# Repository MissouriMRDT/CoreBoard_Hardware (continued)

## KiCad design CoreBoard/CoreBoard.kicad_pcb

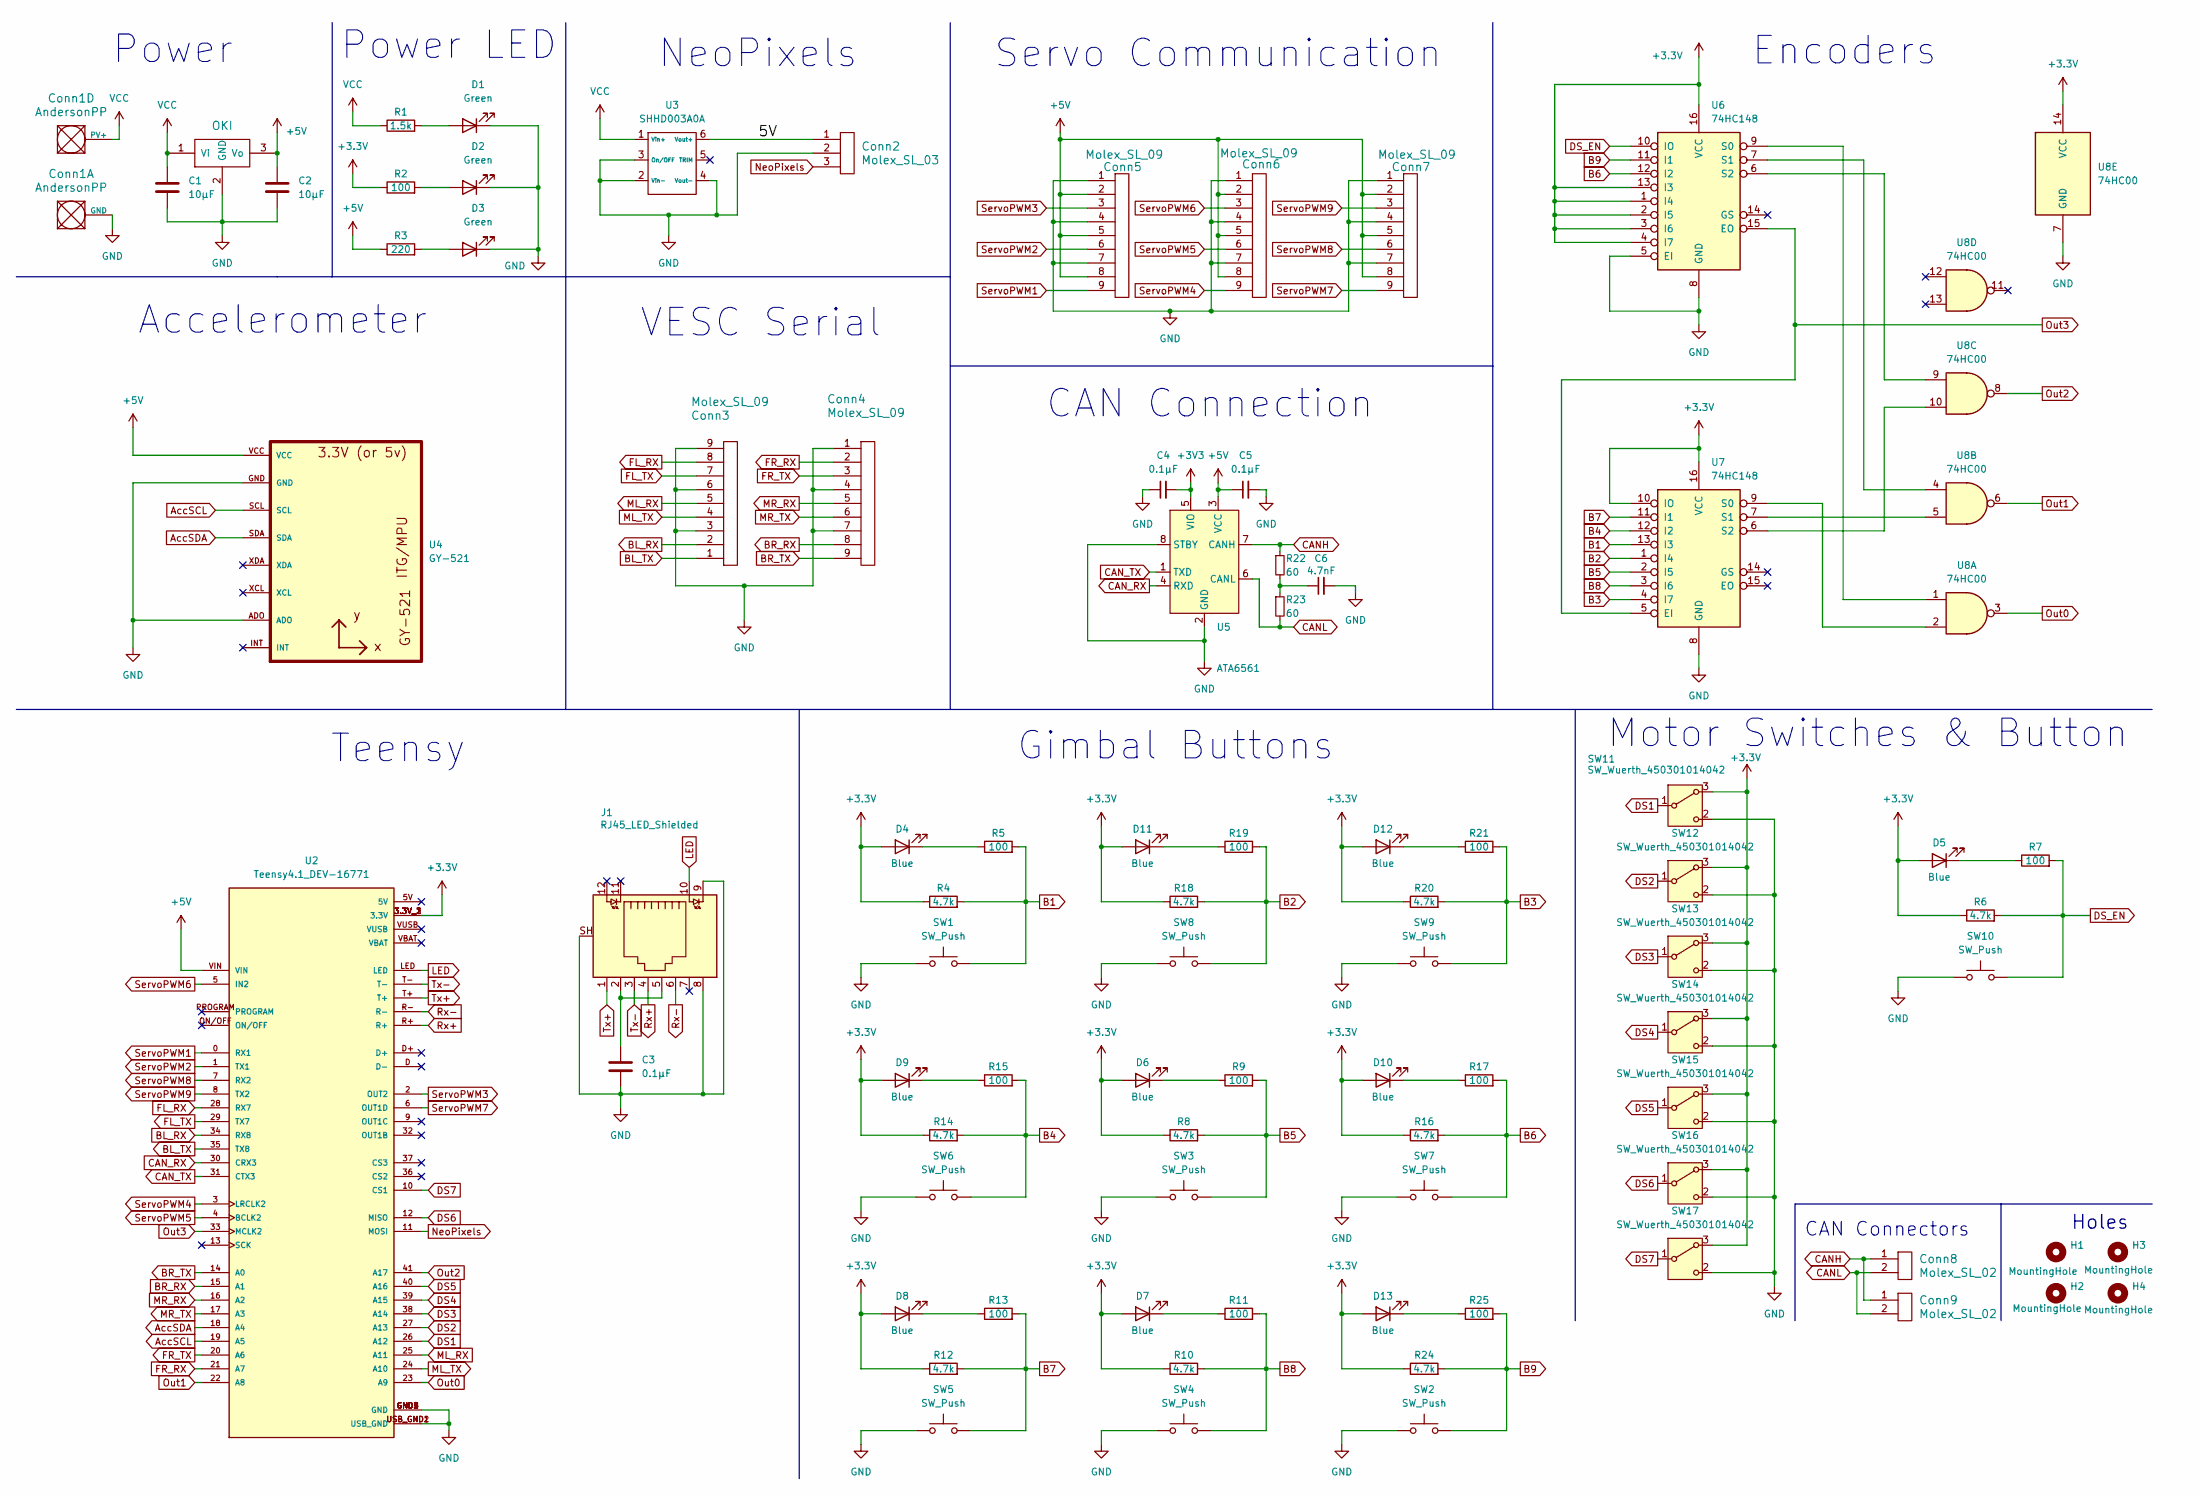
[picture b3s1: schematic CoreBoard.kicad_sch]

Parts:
C1: 10µF; C_1206_3216Metric_Pad1.33x1.80mm_HandSolder
C2: 10µF; C_0603_1608Metric_Pad1.08x0.95mm_HandSolder
C3, C4, C5: 0.1µF; C_0603_1608Metric_Pad1.08x0.95mm_HandSolder
C6: 4.7nF; C_0603_1608Metric_Pad1.08x0.95mm_HandSolder
Conn1: AndersonPP; Square_Anderson_2_H_Side_By_Side_PV
Conn2: Molex_SL_03; MOLEX_SL_03_Vertical
Conn3, Conn4, Conn5, Conn6, Conn7: Molex_SL_09; MOLEX_SL_09_Horizontal
Conn8, Conn9: Molex_SL_02; MOLEX_SL_02_Vertical
D1, D2, D3: Green; LED_0603_1608Metric_Pad1.05x0.95mm_HandSolder
D4, D5, D6, D7, D8, D9, D10, D11, D12, D13: Blue; LED_0603_1608Metric_Pad1.05x0.95mm_HandSolder
H1, H2, H3, H4: MountingHole; 4_40_Hole
J1: RJ45_LED_Shielded; RJ45_Teensy
R1: 1.5k; R_0603_1608Metric_Pad0.98x0.95mm_HandSolder
R2, R5, R7, R9, R11, R13, R15, R17, R19, R21, R25: 100; R_0603_1608Metric_Pad0.98x0.95mm_HandSolder
R3: 220; R_0603_1608Metric_Pad0.98x0.95mm_HandSolder
R4, R6, R8, R10, R12, R14, R16, R18, R20, R24: 4.7k; R_0603_1608Metric_Pad0.98x0.95mm_HandSolder
R22, R23: 60; R_0603_1608Metric_Pad0.98x0.95mm_HandSolder
SW1, SW2, SW3, SW4, SW5, SW6, SW7, SW8, SW9, SW10: SW_Push; SW_SPST_TL3305A
SW11, SW12, SW13, SW14, SW15, SW16, SW17: SW_Wuerth_450301014042; SW_Switch_03_STSSS9121_Through_Hole
U1: OKI; OKI_Horizontal
U2: Teensy4.1_DEV-16771; Teensy_4_1_Ethernet; PARTREV 4.1
U3: SHHD003A0A; SHHD003A0A41Z_Through_Hole
U4: GY-521
U5: ATA6561; SOIC-8_3.9x4.9mm_P1.27mm
U6, U7: 74HC148; SOIC-16_4.55x10.3mm_P1.27mm
U8: 74HC00; SO-14_5.3x10.2mm_P1.27mm

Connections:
+3.3V: D4.2 (A), D5.2 (A), D6.2 (A), D7.2 (A), D8.2 (A), D9.2 (A), D10.2 (A), D11.2 (A), D12.2 (A), D13.2 (A), R2.1, R4.1, R6.1, R8.1, R10.1, R12.1, R14.1, R16.1, R18.1, R20.1, R24.1, SW11.3 (A), SW12.3 (A), SW13.3 (A), SW14.3 (A), SW15.3 (A), SW16.3 (A), SW17.3 (A), U2.3.3V_1 (3.3V), U2.3.3V_2 (3.3V), U2.3.3V_3 (3.3V), U6.1 (I4), U6.2 (I5), U6.3 (I6), U6.4 (I7), U6.13 (I3), U6.16 (VCC), U7.10 (IO), U7.16 (VCC), U8.14 (VCC)
+3V3: C4.2, U5.5 (VIO)
+5V: C2.1, C5.1, Conn5.2, Conn5.5, Conn5.8, Conn6.2, Conn6.5, Conn6.8, Conn7.2, Conn7.5, Conn7.8, R3.1, U1.3 (Vo), U2.VIN, U4.VCC, U5.3 (VCC)
/5V: Conn2.1, U3.6 (Vout+)
AccSCL: U2.19 (A5), U4.SCL
AccSDA: U2.18 (A4), U4.SDA
B1: R4.2, R5.2, SW1.2, U7.13 (I3)
B2: R18.2, R19.2, SW8.2, U7.1 (I4)
B3: R20.2, R21.2, SW9.2, U7.4 (I7)
B4: R14.2, R15.2, SW6.2, U7.12 (I2)
B5: R8.2, R9.2, SW3.2, U7.2 (I5)
B6: R16.2, R17.2, SW7.2, U6.12 (I2)
B7: R12.2, R13.2, SW5.2, U7.11 (I1)
B8: R10.2, R11.2, SW4.2, U7.3 (I6)
B9: R24.2, R25.2, SW2.2, U6.11 (I1)
BL_RX: Conn3.2, U2.34 (RX8)
BL_TX: Conn3.1, U2.35 (TX8)
BR_RX: Conn4.8, U2.15 (A1)
BR_TX: Conn4.9, U2.14 (A0)
CANH: Conn8.1, Conn9.1, R22.1, U5.7 (CANH)
CANL: Conn8.2, Conn9.2, R23.2, U5.6 (CANL)
CAN_RX: U2.30 (CRX3), U5.4 (RXD)
CAN_TX: U2.31 (CTX3), U5.1 (TXD)
DS1: SW11.1 (B), U2.26 (A12)
DS2: SW12.1 (B), U2.27 (A13)
DS3: SW13.1 (B), U2.38 (A14)
DS4: SW14.1 (B), U2.39 (A15)
DS5: SW15.1 (B), U2.40 (A16)
DS6: SW16.1 (B), U2.12 (MISO)
DS7: SW17.1 (B), U2.10 (CS1)
DS_EN: R6.2, R7.2, SW10.2, U6.10 (IO)
FL_RX: Conn3.8, U2.28 (RX7)
FL_TX: Conn3.7, U2.29 (TX7)
FR_RX: Conn4.2, U2.21 (A7)
FR_TX: Conn4.3, U2.20 (A6)
GND: C1.2, C2.2, C3.2, C4.1, C5.2, C6.2, Conn1.1 (GND), Conn2.2, Conn3.3, Conn3.6, Conn3.9, Conn4.1, Conn4.4, Conn4.7, Conn5.1, Conn5.4, Conn5.7, Conn6.1, Conn6.4, Conn6.7, Conn7.1, Conn7.4, Conn7.7, D1.1 (K), D2.1 (K), D3.1 (K), J1.8, J1.9, J1.SH, SW1.1, SW2.1, SW3.1, SW4.1, SW5.1, SW6.1, SW7.1, SW8.1, SW9.1, SW10.1, SW11.2 (C), SW12.2 (C), SW13.2 (C), SW14.2 (C), SW15.2 (C), SW16.2 (C), SW17.2 (C), U1.2 (GND), U2.GND1 (GND), U2.GND2 (GND), U2.GND3 (GND), U2.GND4 (GND), U2.GND5 (GND), U2.USB_GND1 (USB_GND), U2.USB_GND2 (USB_GND), U3.2 (Vin-), U3.3 (On/OFF), U3.4 (Vout-), U4.ADO, U4.GND, U5.2 (GND), U5.8 (STBY), U6.5 (EI), U6.8 (GND), U7.8 (GND), U8.7 (GND)
LED: J1.10, U2.LED
ML_RX: Conn3.5, U2.25 (A11)
ML_TX: Conn3.4, U2.24 (A10)
MR_RX: Conn4.5, U2.16 (A2)
MR_TX: Conn4.6, U2.17 (A3)
NeoPixels: Conn2.3, U2.11 (MOSI)
unnamed: C3.1, J1.2, J1.5
unnamed: C6.1, R22.2, R23.1
unnamed: D1.2 (A), R1.2
unnamed: D2.2 (A), R2.2
unnamed: D3.2 (A), R3.2
unnamed: D4.1 (K), R5.1
unnamed: D5.1 (K), R7.1
unnamed: D6.1 (K), R9.1
unnamed: D7.1 (K), R11.1
unnamed: D8.1 (K), R13.1
unnamed: D9.1 (K), R15.1
unnamed: D10.1 (K), R17.1
unnamed: D11.1 (K), R19.1
unnamed: D12.1 (K), R21.1
unnamed: D13.1 (K), R25.1
unnamed: U6.9 (S0), U8.1
unnamed: U6.7 (S1), U8.4
unnamed: U6.6 (S2), U8.9
unnamed: U7.9 (S0), U8.2
unnamed: U7.7 (S1), U8.5
unnamed: U7.6 (S2), U8.10
Out0: U2.23 (A9), U8.3
Out1: U2.22 (A8), U8.6
Out2: U2.41 (A17), U8.8
Out3: U2.33 (MCLK2), U6.15 (EO), U7.5 (EI)
Rx+: J1.4, U2.R+
Rx-: J1.6, U2.R-
ServoPWM1: Conn5.9, U2.0 (RX1)
ServoPWM2: Conn5.6, U2.1 (TX1)
ServoPWM3: Conn5.3, U2.2 (OUT2)
ServoPWM4: Conn6.9, U2.3 (LRCLK2)
ServoPWM5: Conn6.6, U2.4 (BCLK2)
ServoPWM6: Conn6.3, U2.5 (IN2)
ServoPWM7: Conn7.9, U2.6 (OUT1D)
ServoPWM8: Conn7.6, U2.7 (RX2)
ServoPWM9: Conn7.3, U2.8 (TX2)
Tx+: J1.1, U2.T+
Tx-: J1.3, U2.T-
VCC: C1.1, Conn1.4 (PV+), R1.1, U1.1 (Vi), U3.1 (Vin+)

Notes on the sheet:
Power
CAN Connection
Power LED
Gimbal Buttons
Accelerometer
Motor Switches & Button
Servo Communication
VESC Serial
Teensy
Encoders
CAN Connectors
NeoPixels
Holes

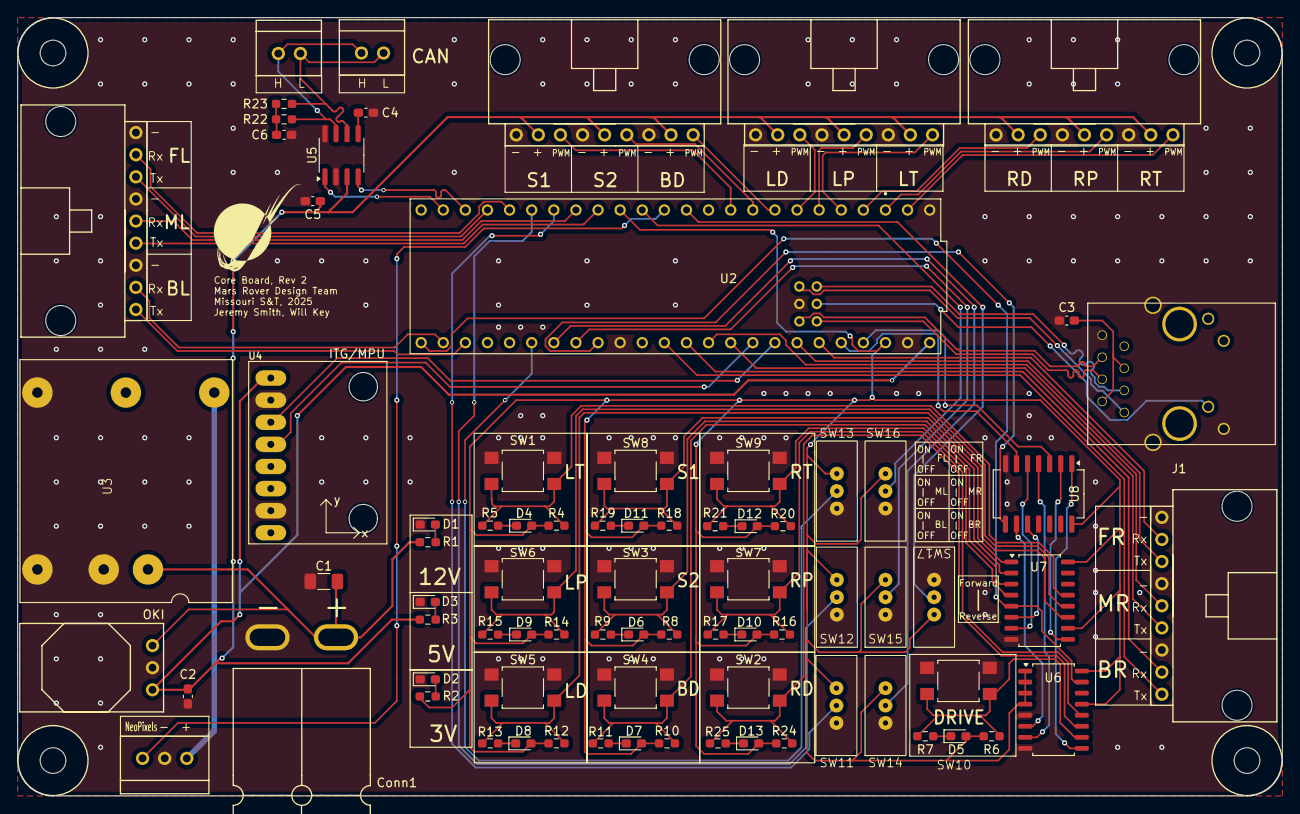
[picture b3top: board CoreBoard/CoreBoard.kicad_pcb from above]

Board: 2 copper layers, 145.3 x 89.4 mm, 83 parts (0 on the bottom side), 81 nets.

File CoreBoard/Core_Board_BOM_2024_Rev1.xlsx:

Designator | Package | Value | Item Name | Manufacturer number | Part Number | Vendor | Quantity | Cost Per Item | Cost | URL
C1,C2 |  | 10µF |  |  |  |  | 2
C3 |  | 0.1µF |  |  |  |  | 1
C4,C5 |  | 100nF |  |  |  |  | 2
C6 |  | 4.7nF |  |  |  |  | 1
Conn1 |  | AndersonPP |  |  |  |  | 1
Conn2 |  | Molex_SL_03 |  |  |  |  | 1
Conn3,Conn4,Conn5,Conn6,Conn7 |  | Molex_SL_09 |  |  |  |  | 5
D1,D2,D3 |  | Green |  |  |  |  | 3
D4,D5,D6,D7,D8,D9,D10,D11,D12,D13 |  | Blue |  |  |  |  | 10
J1 |  | RJ45_LED_Shielded |  |  |  |  | 1
R1 |  | 1.5k? |  |  |  |  | 1
R2,R5,R7,R9,R11,R13,R15,R17,R19,R21,R25 |  | 100? |  |  |  |  | 11
R3 |  | 200? |  |  |  |  | 1
R4,R6,R8,R10,R12,R14,R16,R18,R20,R24 |  | 4.7k? |  |  |  |  | 10
R22,R23 |  | 60? |  |  |  |  | 2
SW1,SW2,SW3,SW4,SW5,SW6,SW7,SW8,SW9,SW10 |  | SW_Push |  |  |  |  | 10
SW12 |  | SW_DIP_x07 |  |  |  |  | 1
U1 |  | OKI |  |  |  |  | 1
U2 |  | Teensy4.1_DEV-16771 |  |  |  |  | 1
U3 |  | SHHD003A0A |  |  |  |  | 1
U4 |  | GY-521 |  |  |  |  | 1
U5 |  | ATA6561 |  |  |  |  | 1
U6,U7 |  | 74HC148 |  |  |  |  | 2
U8 |  | 74HC00 |  |  |  |  | 1

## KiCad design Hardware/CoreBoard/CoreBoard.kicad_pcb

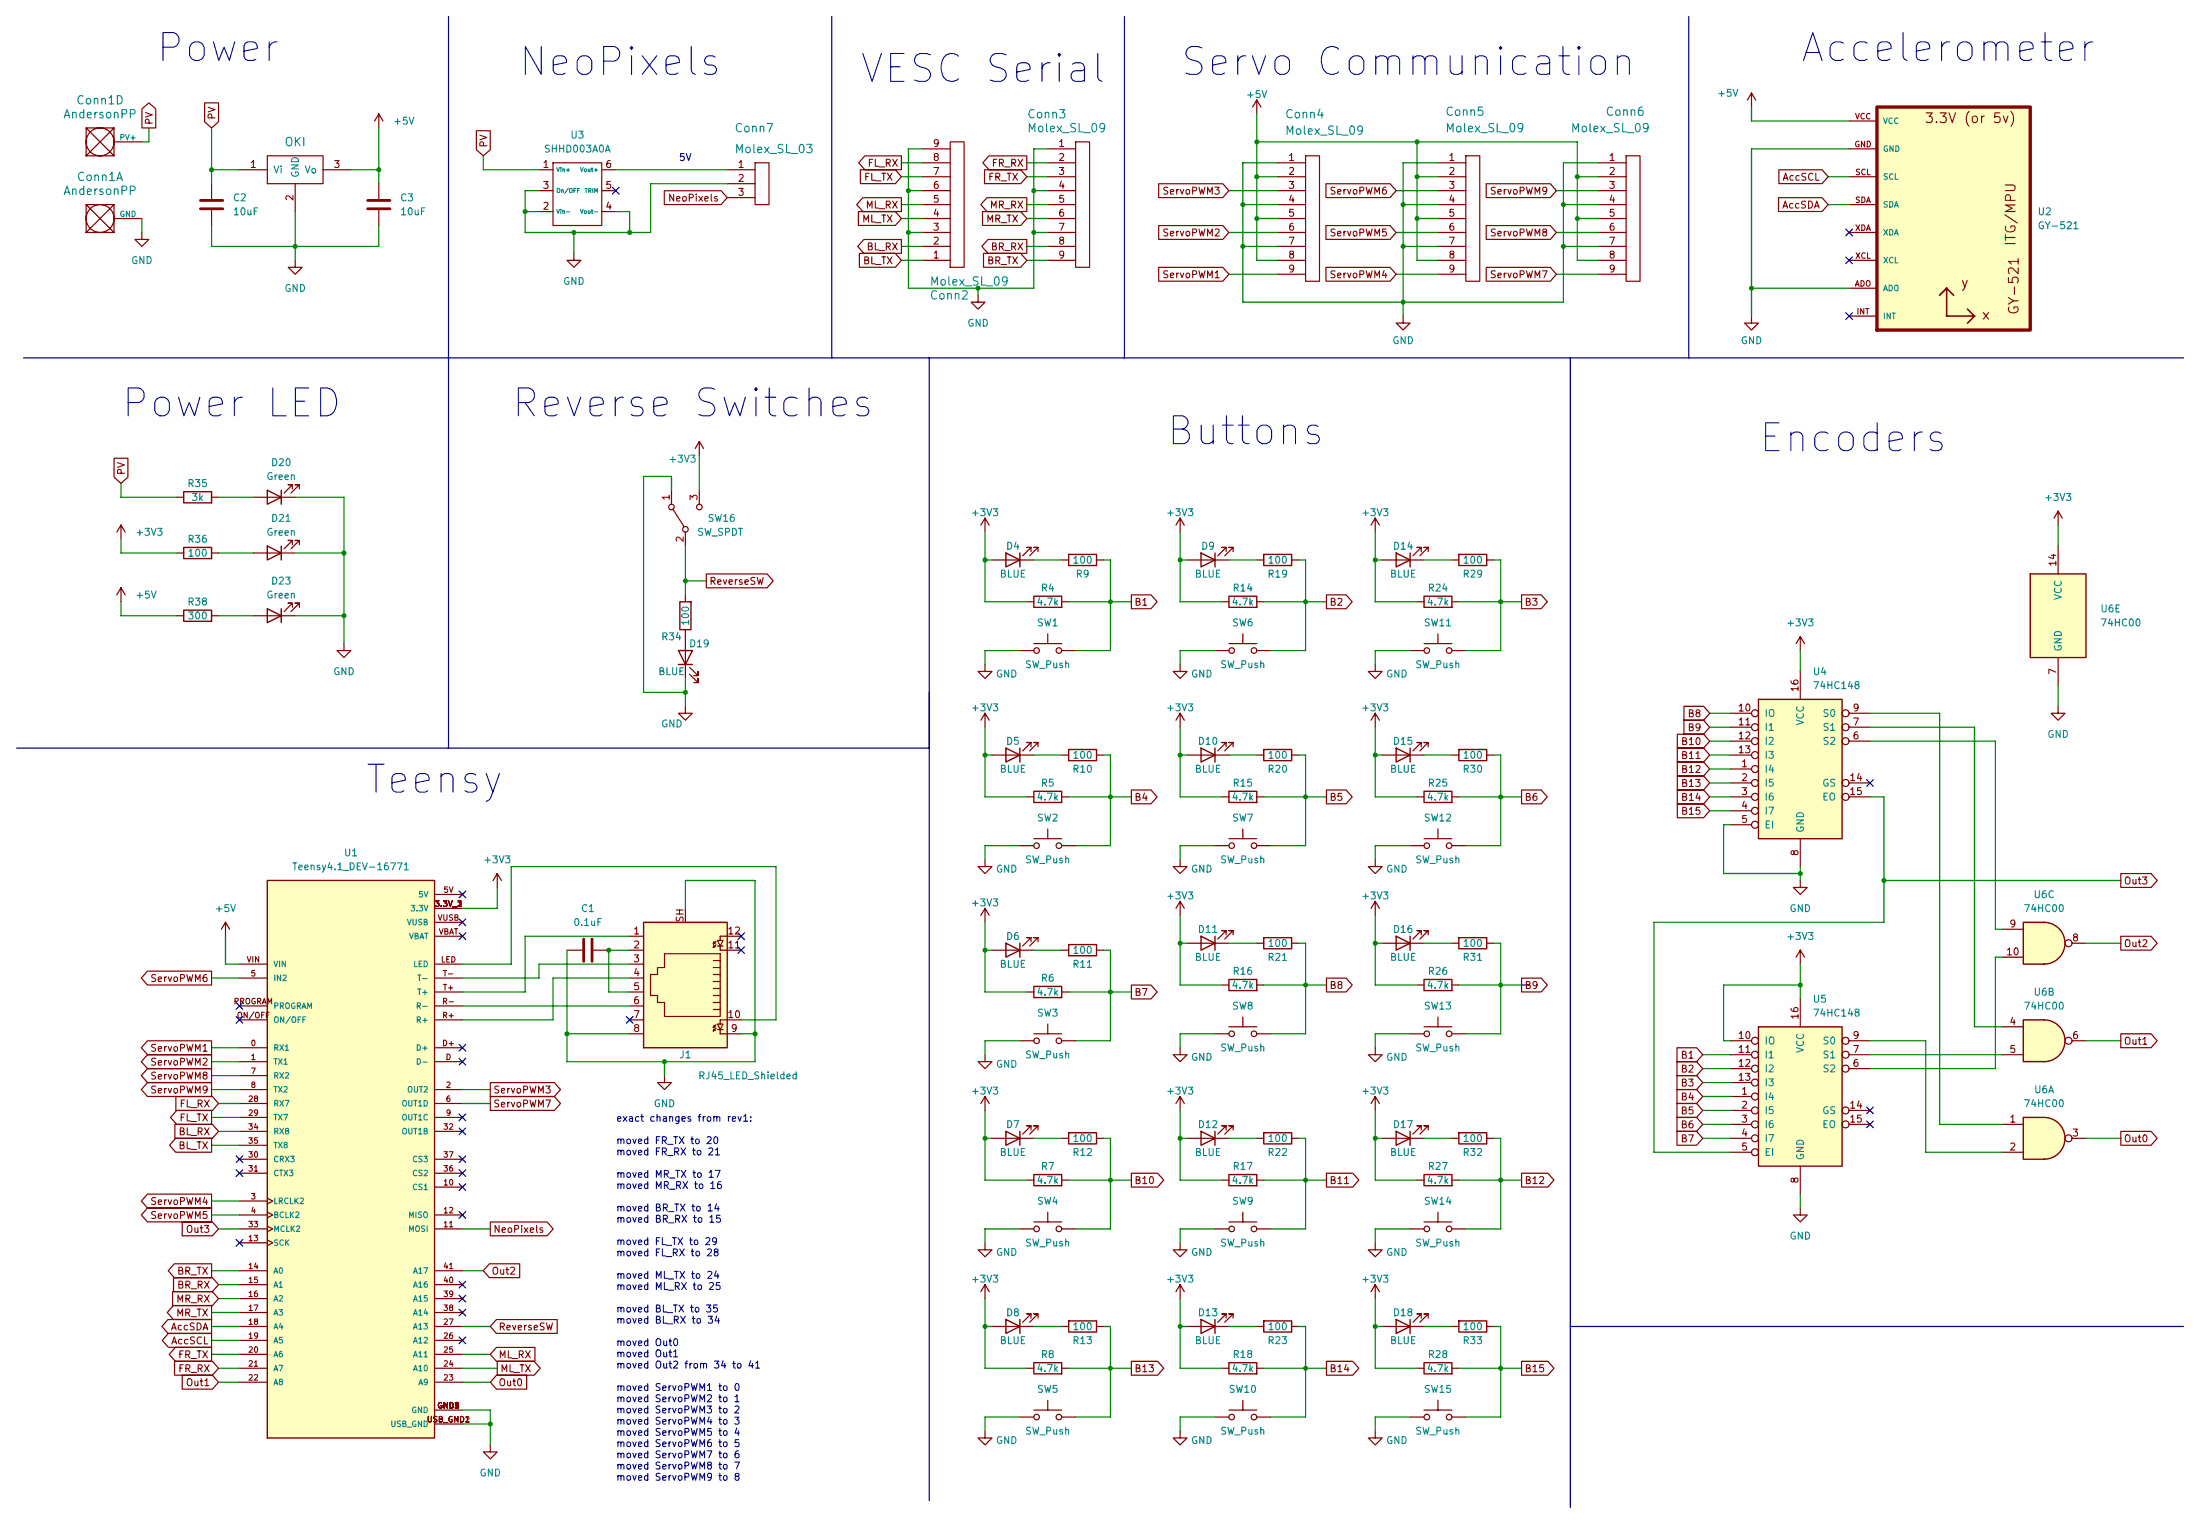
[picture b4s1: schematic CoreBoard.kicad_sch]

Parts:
C1: 0.1uF; C_0603_1608Metric_Pad1.08x0.95mm_HandSolder
C2: 10uF; C_1206_3216Metric_Pad1.33x1.80mm_HandSolder
C3: 10uF; C_0603_1608Metric_Pad1.08x0.95mm_HandSolder
Conn1: AndersonPP; Square_Anderson_2_H_Side_By_Side_PV
Conn2, Conn3, Conn4, Conn5, Conn6: Molex_SL_09; MOLEX_SL_09_Horizontal
Conn7: Molex_SL_03; MOLEX_SL_03_Vertical
D4, D5, D6, D7, D8, D9, D10, D11, D12, D13, D14, D15, D16, D17, D18, D19: BLUE; LED_0603_1608Metric_Pad1.05x0.95mm_HandSolder
D20, D21, D23: Green; LED_0603_1608Metric_Pad1.05x0.95mm_HandSolder
J1: RJ45_LED_Shielded; RJ45_Teensy
R4, R5, R6, R7, R8, R14, R15, R16, R17, R18, R24, R25, R26, R27, R28: 4.7k; R_0603_1608Metric_Pad0.98x0.95mm_HandSolder
R9, R10, R11, R12, R13, R19, R20, R21, R22, R23, R29, R30, R31, R32, R33, R34, R36: 100; R_0603_1608Metric_Pad0.98x0.95mm_HandSolder
R35: 3k; R_0603_1608Metric_Pad0.98x0.95mm_HandSolder
R38: 300; R_0603_1608Metric_Pad0.98x0.95mm_HandSolder
SW1, SW2, SW3, SW4, SW5, SW6, SW7, SW8, SW9, SW10, SW11, SW12, SW13, SW14, SW15: SW_Push; SW_SPST_TL3305A
SW16: SW_SPDT; SW_Slide_1P2T_CK_OS102011MS2Q
U1: Teensy4.1_DEV-16771; Teensy_4_1_Ethernet; PARTREV 4.1
U2: GY-521
U3: SHHD003A0A; SHHD003A0A-SRZ
U4, U5: 74HC148; SOIC-16_4.55x10.3mm_P1.27mm
U6: 74HC00; SO-14_5.3x10.2mm_P1.27mm
U7: OKI; OKI_Horizontal

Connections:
+3V3: D4.2 (A), D5.2 (A), D6.2 (A), D7.2 (A), D8.2 (A), D9.2 (A), D10.2 (A), D11.2 (A), D12.2 (A), D13.2 (A), D14.2 (A), D15.2 (A), D16.2 (A), D17.2 (A), D18.2 (A), R4.1, R5.1, R6.1, R7.1, R8.1, R14.1, R15.1, R16.1, R17.1, R18.1, R24.1, R25.1, R26.1, R27.1, R28.1, R36.1, SW16.3 (C), U1.3.3V_1 (3.3V), U1.3.3V_2 (3.3V), U1.3.3V_3 (3.3V), U4.16 (VCC), U5.10 (IO), U5.16 (VCC), U6.14 (VCC)
+5V: C3.1, Conn4.2, Conn4.5, Conn4.8, Conn5.2, Conn5.5, Conn5.8, Conn6.2, Conn6.5, Conn6.8, R38.1, U1.VIN, U2.VCC, U7.3 (Vo)
AccSCL: U1.19 (A5), U2.SCL
AccSDA: U1.18 (A4), U2.SDA
B1: R4.2, R9.1, SW1.2, U5.11 (I1)
B2: R14.2, R19.1, SW6.2, U5.12 (I2)
B3: R24.2, R29.1, SW11.2, U5.13 (I3)
B4: R5.2, R10.1, SW2.2, U5.1 (I4)
B5: R15.2, R20.1, SW7.2, U5.2 (I5)
B6: R25.2, R30.1, SW12.2, U5.3 (I6)
B7: R6.2, R11.1, SW3.2, U5.4 (I7)
B8: R16.2, R21.1, SW8.2, U4.10 (IO)
B9: R26.2, R31.1, SW13.2, U4.11 (I1)
B10: R7.2, R12.1, SW4.2, U4.12 (I2)
B11: R17.2, R22.1, SW9.2, U4.13 (I3)
B12: R27.2, R32.1, SW14.2, U4.1 (I4)
B13: R8.2, R13.1, SW5.2, U4.2 (I5)
B14: R18.2, R23.1, SW10.2, U4.3 (I6)
B15: R28.2, R33.1, SW15.2, U4.4 (I7)
BL_RX: Conn2.2, U1.34 (RX8)
BL_TX: Conn2.1, U1.35 (TX8)
BR_RX: Conn3.8, U1.15 (A1)
BR_TX: Conn3.9, U1.14 (A0)
FL_RX: Conn2.8, U1.28 (RX7)
FL_TX: Conn2.7, U1.29 (TX7)
FR_RX: Conn3.2, U1.21 (A7)
FR_TX: Conn3.3, U1.20 (A6)
GND: C1.1, C2.2, C3.2, Conn1.1 (GND), Conn2.3, Conn2.6, Conn2.9, Conn3.1, Conn3.4, Conn3.7, Conn4.1, Conn4.4, Conn4.7, Conn5.1, Conn5.4, Conn5.7, Conn6.1, Conn6.4, Conn6.7, Conn7.2, D19.1 (K), D20.1 (K), D21.1 (K), D23.1 (K), J1.8, J1.9, J1.SH, SW1.1, SW2.1, SW3.1, SW4.1, SW5.1, SW6.1, SW7.1, SW8.1, SW9.1, SW10.1, SW11.1, SW12.1, SW13.1, SW14.1, SW15.1, SW16.1 (A), U1.GND1 (GND), U1.GND2 (GND), U1.GND3 (GND), U1.GND4 (GND), U1.GND5 (GND), U1.USB_GND1 (USB_GND), U1.USB_GND2 (USB_GND), U2.ADO, U2.GND, U3.2 (Vin-), U3.3 (On/OFF), U3.4 (Vout-), U4.5 (EI), U4.8 (GND), U5.8 (GND), U6.7 (GND), U7.2 (GND)
ML_RX: Conn2.5, U1.25 (A11)
ML_TX: Conn2.4, U1.24 (A10)
MR_RX: Conn3.5, U1.16 (A2)
MR_TX: Conn3.6, U1.17 (A3)
NeoPixels: Conn7.3, U1.11 (MOSI)
unnamed: C1.2, J1.2, J1.5
unnamed: D4.1 (K), R9.2
unnamed: D5.1 (K), R10.2
unnamed: D6.1 (K), R11.2
unnamed: D7.1 (K), R12.2
unnamed: D8.1 (K), R13.2
unnamed: D9.1 (K), R19.2
unnamed: D10.1 (K), R20.2
unnamed: D11.1 (K), R21.2
unnamed: D12.1 (K), R22.2
unnamed: D13.1 (K), R23.2
unnamed: D14.1 (K), R29.2
unnamed: D15.1 (K), R30.2
unnamed: D16.1 (K), R31.2
unnamed: D17.1 (K), R32.2
unnamed: D18.1 (K), R33.2
unnamed: D19.2 (A), R34.1
unnamed: D20.2 (A), R35.2
unnamed: D21.2 (A), R36.2
unnamed: D23.2 (A), R38.2
unnamed: J1.1, U1.T+
unnamed: J1.3, U1.T-
unnamed: J1.4, U1.R+
unnamed: J1.6, U1.R-
unnamed: J1.10, U1.LED
unnamed: Conn7.1, U3.6 (Vout+)
unnamed: U4.9 (S0), U6.1
unnamed: U4.7 (S1), U6.4
unnamed: U4.6 (S2), U6.9
unnamed: U5.9 (S0), U6.2
unnamed: U5.7 (S1), U6.5
unnamed: U5.6 (S2), U6.10
Out0: U1.23 (A9), U6.3
Out1: U1.22 (A8), U6.6
Out2: U1.41 (A17), U6.8
Out3: U1.33 (MCLK2), U4.15 (EO), U5.5 (EI)
PV: C2.1, Conn1.4 (PV+), R35.1, U3.1 (Vin+), U7.1 (Vi)
ReverseSW: R34.2, SW16.2 (B), U1.27 (A13)
ServoPWM1: Conn4.9, U1.0 (RX1)
ServoPWM2: Conn4.6, U1.1 (TX1)
ServoPWM3: Conn4.3, U1.2 (OUT2)
ServoPWM4: Conn5.9, U1.3 (LRCLK2)
ServoPWM5: Conn5.6, U1.4 (BCLK2)
ServoPWM6: Conn5.3, U1.5 (IN2)
ServoPWM7: Conn6.9, U1.6 (OUT1D)
ServoPWM8: Conn6.6, U1.7 (RX2)
ServoPWM9: Conn6.3, U1.8 (TX2)

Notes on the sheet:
Teensy
Accelerometer
Reverse Switches
NeoPixels
exact changes from rev1: moved FR_TX to 20 moved FR_RX to 21 moved MR_TX to 17 moved MR_RX to 16 moved BR_TX to 14 moved BR_RX to 15 moved FL_TX to 29 moved FL_RX to 28 moved ML_TX to 24 moved ML_RX to 25 moved BL_TX to 35 moved BL_RX to 34 moved Out0 moved Out1 moved Out2 from 34 to 41 moved Servo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
Power
Buttons
Power LED
Servo Communication
Encoders
VESC Serial

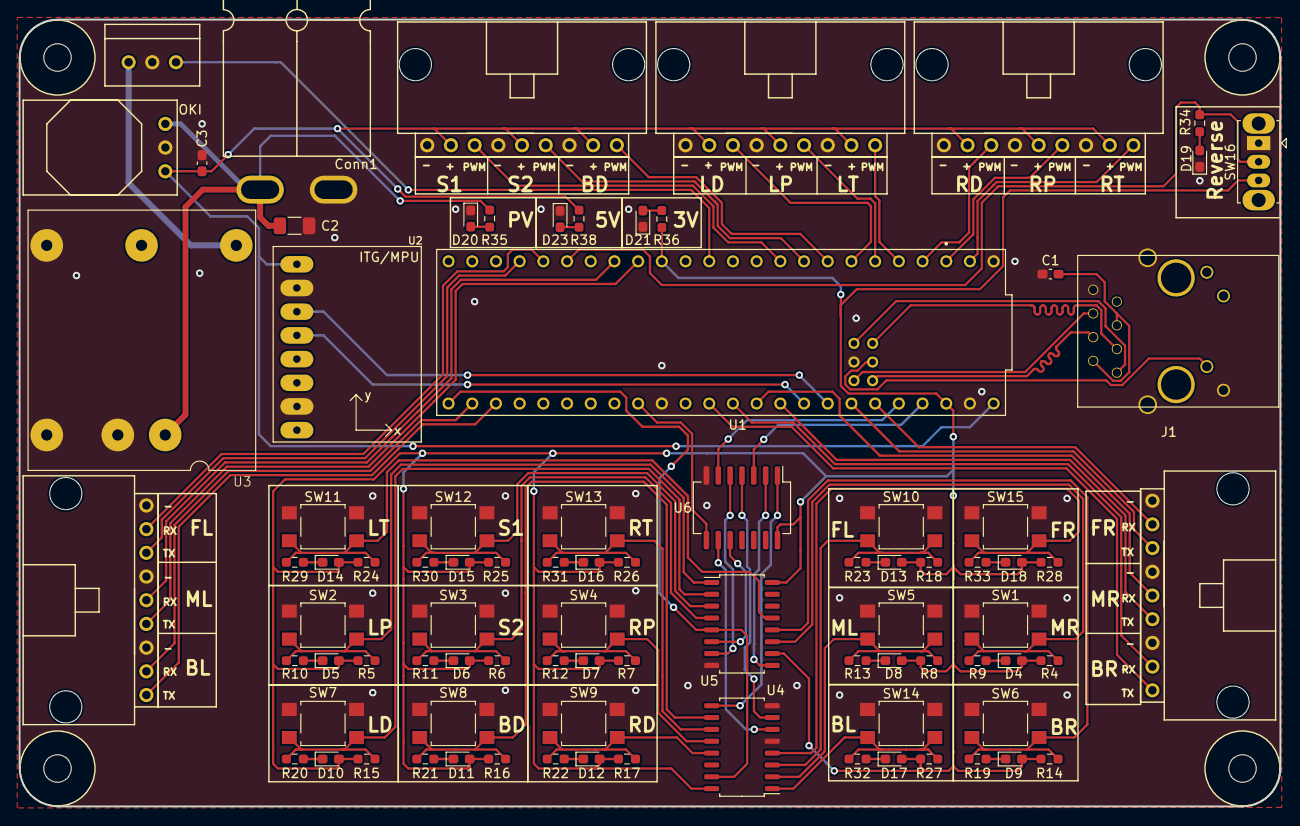
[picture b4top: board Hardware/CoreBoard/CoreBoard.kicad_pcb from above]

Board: 2 copper layers, 135.1 x 84.3 mm, 87 parts (0 on the bottom side), 80 nets.

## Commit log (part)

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2023-04-27 moved coreboard CAD and documentation to proper repository
2023-09-13 adding initial file
2023-09-13 Initial Simple Circuits
2023-09-14 Added symbols based on requirements
2023-09-14 Added Serial Ports for VESCS
2023-09-16 Changes to Converter
2023-09-16 added buttons, lights, and a few other things from last year's board
2023-09-21 Changes to Schematic
2023-09-21 figured out buttons, deleted some leds
2023-09-24 Tweaks to Schematic
    - Finished the encoders for the buttons.
    - Final attachments to the Teensy
    - Organization of schematic
2023-09-25 BOM Generated in Directory
2023-09-25 Changes to LED Resistance value
2023-09-25 Encoder Outputs in Teensy, Reverse Input
2023-09-26 Review Fixes
2023-09-30 Changes to OKI, BOM Regeneration
2023-10-16 completed rev1 rough draft
2023-10-18 re-did board
2023-10-18 More Buttons
2023-10-19 More Encoder Work
2023-10-20 connected remaining components
2023-10-20 more aligning
2023-10-20 all but logo (allegedly)
2023-10-21 Logo and Names Added to Layout
2023-10-24 Changes to Labels
2023-10-24 updating button traces
2023-10-24 Signatures Added
2023-11-01 Layout Changes
2023-11-02 Gerbs Generated
2023-11-08 Layout Edits
2023-11-16 Generated STEP File
2024-03-07 first rev2 commit
2024-03-07 added old boards
2024-03-07 put enable pins on encoders to ground
2024-03-07 fixed file structure
2024-03-07 fixing file structure
2024-03-08 made rev2 changes and cleaned up traces
2024-03-08 re-upload, didn't save last time
2024-03-15 changed according to discord message
2024-03-20 flipped pwm labels and organized servos by right/left
2024-03-20 added accelerometer and touch-ups
2024-03-21 finished adding accelerometer
2024-03-23 added grounding vias in center
2024-03-26 generated gerbs
2024-04-03 Created step file
2024-04-05 Fixed STEP files
2024-09-24 Start
2024-09-24 Placed in basic components for power, the Teensy, and ethernet
2024-09-24 Added connections between the Teensy and the Ethernet Port, and the capacitance values were added for capacitors
2024-09-26 Added Power LEDs and one button
2024-09-26 Increased the size of the schematic and added remaining buttons, resistor values for buttons may need to be redone
2024-09-26 Added more headings for future sections of the schematic
2024-09-27 Added NeoPixel Schematic
2024-09-27 Added the schematics for the VESC Serial Connections and the Accelerometer
2024-09-27 Servo communication
2024-09-30 Small changes
2024-10-01 Added CAN Transmitter
2024-10-04 Added Encoders, 8 switch dipswitch, and Teensy inputs and outputs
2024-10-04 Added CAN connections to Teensy
2024-10-05 Added connections from the dip switch and button to the Teensy, and from the Teensy to the encoder. Schematics should be finished for now
2024-10-08 Swapped 200 ohm resistor for 220 ohm resistor
2024-10-08 Changed 100nF capacitors to 0.1µF capacitors
2024-10-08 Added mounting holes
2024-10-08 added gitignore
2024-10-08 removed backup files
2024-10-15 Fixed many things from schematic review, VCC power flags, no connects, added a 4th NAND gate, changed labels to text, changed DS8 tag to DS_EN, and removed the standby tag from the CAN transceiver to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
2024-10-22 Added CAN Connectors
2024-10-22 Added footprints to the majority of components on the schematic
2024-10-23 Just a test
2024-10-23 Test 2
2024-10-24 Created initial PCB layout, and put in majority of components
2024-10-28 Added ground layer to layout
2024-10-28 Layout has been changed to group components together similar to the style of the schematic for better connections, and the footprint for the OKI for the NeoPixels has been changed
2024-10-28 Something
2024-10-29 Added footprints for mounting holes
2024-10-29 Rearranged layout for better off-board wire arrangement
2024-10-29 Changed footprint of NeoPixels to a though hole, and added some wires
2024-10-29 Added Some Outputs
    Need to find an 12 pin output.
2024-10-31 Nearly completed first draft of the layout, and adjusted the schematic for easier routing
2024-10-31 Fixed 90 degree traces, finished routing unconnected traces, placed ground vias to connect other unrouted traces/pads, and added silkscreen labels and header to the layout
2024-10-31 Fixed trace width near CAN connections, were too narrow due to nearby vias
2024-11-01 Added silkscreens for NeoPixel and CAN SLs
2024-11-05 Changed silkscreen for CAN SLs from "+" and "-" to "H" and "L"
2024-11-05 Rearranged CAN layout and merged traces near the Anderson
2024-11-06 Adjusted CAN Rx and Tx trace length
2024-11-07 Shifted ethernet port and traces down the board as to not interfere with the Teensy USB port, and changed the layers on which several traces run to free up the ground plane near the ground anderson
2024-11-07 Changed Schematic Heading for Switches
2024-11-08 Fixed silkscreens problems raised in CDR; switch labels and power label
2024-11-12 Added vias to get rid of ground voids and added a mounting hole as a standoff for the accelerometer
2024-11-14 Removed extra 5V via
2024-11-15 Created Manufacturing files, adjusted mounting holes, and added standoff holes for accelerometer
2025-02-28 Creating rev2 branch
2025-02-28 Created rev2 schematic, changed switches to prevent short, and changed encoder no-connects to 3.3V
2025-03-07 Created updated PCB from new rev_2 schematic
2025-03-17 Update CoreBoard.kicad_pcb
    Final rev2 changes
2025-09-06 Removed manufacture folder
2025-09-12 Add workflow
2025-10-14 Finished the teensy pins I think
    Imported decoder and set up pins for it, also I made a general layout
2025-10-14 Converted schematic to hierarchical sheets
2025-10-15 Added Temp Sensor
2025-10-15 Added Rotary Encoder
2025-10-16 Selection LEDs
2025-10-24 Fan, Light, Buck
2025-10-29 Added most Footprints, Schematic review touch up
2025-10-31 temp sense footprint
2025-10-31 Fix accelerometer not imported properly
2025-10-31 rotary footprint
2025-11-02 routed core board
2025-11-02 added 3d model for rotary encoder
2025-11-11 route
2025-11-14 pcb refine
2025-11-16 Added Silkscreen and Pullup to both schematic and layout
2025-11-18 Cleaned up traces and silkscreens
2025-12-10 Updated Megafit 3D model
2026-03-17 Preliminary changes for rev2
2026-03-19 rev2 progress
2026-03-20 move things for buck circuit
2026-03-20 add athena silkscreen
2026-03-20 Add plated mounting holes and buck converter
2026-03-21 add voltage selection jumpers on servos
2026-03-22 fix skew on ethernet diff pairs
2026-03-23 Final board as manufactured
2026-03-23 Design as ordered
